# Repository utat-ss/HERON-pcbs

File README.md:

# Printed Circuit Boards (PCBs)

This repository houses Altium PCB designs for the Heron MK II CubeSat project. It contains [pcbs-common](https://github.com/HeronMkII/pcbs-common) as a Git submodule with commonly used schematics.

**Export all schematics and board layouts to PDF files so others can easily view them without using Altium.**

## How to add pcbs-common files into your current Altium project

- Update your GitHub with the pcbs-common submodule

- Run these git commands from your `./pcbs` folder:

```
git submodule init .
git submodule update --remote pcbs-common
```

- Get the files in your current project
- Project → Add Existing to Project → navigate to your copy of pcbs-common → select relevant files for your design.
- Substitute your current subsheets with the pcbs-common versions
- Open properties of target subsheet (the green box) → find the label indicating from where it’s taking the current subsheet → select the ... → navigate to the pcbs-common version in your project → select and OK
- Synchronize the labels to the subsheet with pcbs-common version
- Right click on the green box → sheet actions → synchronize sheet labels → select the pairs of corresponding sheet symbols → select the bottom arrow option (symbol of a beige box to a blue box [this pushes the version from pcbs-common onto the upper level]).
- When you run out of things to link, select the remaining items in the middle column → add (bottom option) → add no ERCs (X symbols) to pins you are not currently using.

## Updating pcbs-common

From the `pcbs` folder:

`$ git submodule update --remote`

This will fetch the latest commit of `pcbs-common` and update your files.

If you get an error about having modified files inside the `pcbs-common` folder, run the following:

```
$ cd pcbs-common
$ git reset --hard
```

This will discard all local changes you have made in the `pcbs-common` folder. Then, run `$ git submodule update --remote` again to download the most updated version of the `pcbs-common` files.

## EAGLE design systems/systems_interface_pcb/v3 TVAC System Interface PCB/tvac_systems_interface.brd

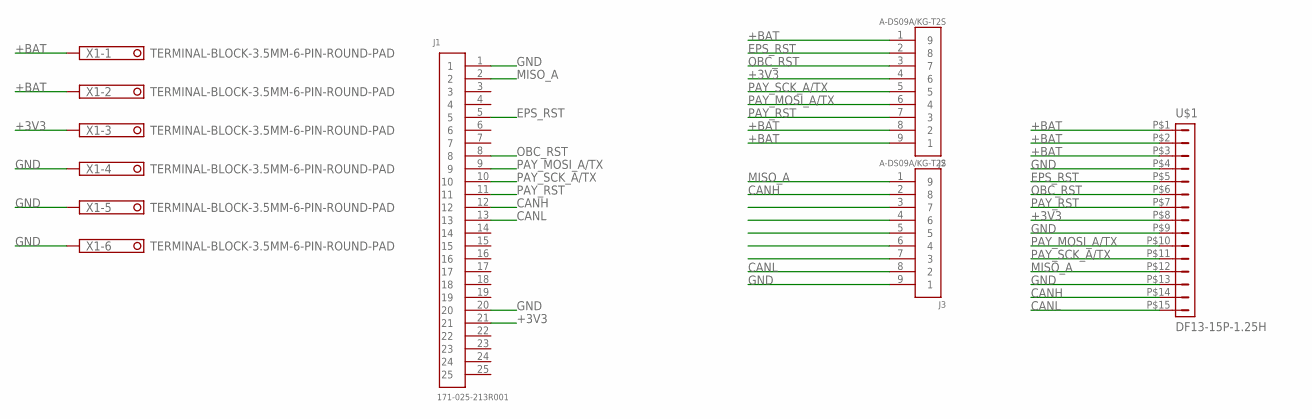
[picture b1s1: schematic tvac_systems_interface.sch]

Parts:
J1: 171-025-213R001
J2, J3: A-DS09A/KG-T2S
U$1: DF13-15P-1.25H; DF13A-15P-1.25H
X1: TERMINAL-BLOCK-3.5MM-6-PIN-ROUND-PAD; TERMINAL-BLOCK-6-PIN-3.5MM-ROUND-PAD

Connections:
+3V3: J1.21, J2.4 (6), U$1.P$8 (8), X1.3
+BAT: J2.1 (9), J2.8 (2), J2.9 (1), U$1.P$1 (1), U$1.P$2 (2), U$1.P$3 (3), X1.1, X1.2
CANH: J1.12, J3.2 (8), U$1.P$14 (14)
CANL: J1.13, J3.8 (2), U$1.P$15 (15)
EPS_RST: J1.5, J2.2 (8), U$1.P$5 (5)
GND: J1.1, J1.20, J3.9 (1), U$1.P$4 (4), U$1.P$9 (9), U$1.P$13 (13), X1.4, X1.5, X1.6
MISO_A: J1.2, J3.1 (9), U$1.P$12 (12)
OBC_RST: J1.8, J2.3 (7), U$1.P$6 (6)
PAY_MOSI_A/TX: J1.9, J2.6 (4), U$1.P$10 (10)
PAY_RST: J1.11, J2.7 (3), U$1.P$7 (7)
PAY_SCK_A/TX: J1.10, J2.5, U$1.P$11 (11)

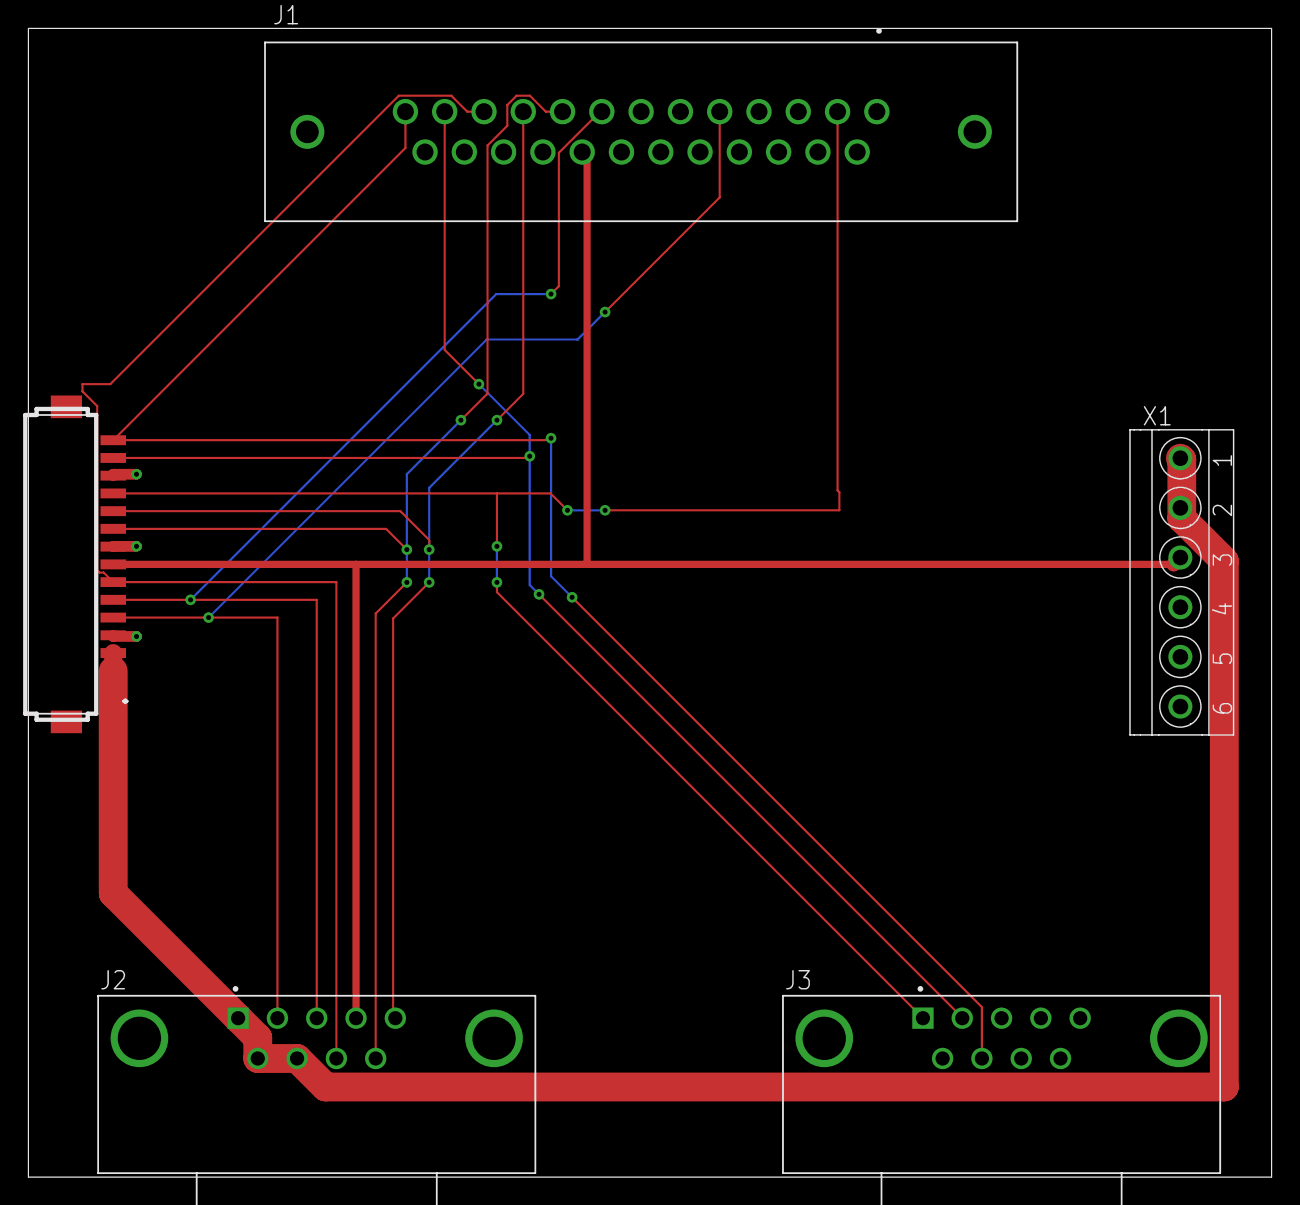
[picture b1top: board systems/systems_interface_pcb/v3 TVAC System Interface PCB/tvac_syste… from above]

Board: 2 copper layers, 87.6 x 81.0 mm, 5 parts (0 on the bottom side), 11 nets.

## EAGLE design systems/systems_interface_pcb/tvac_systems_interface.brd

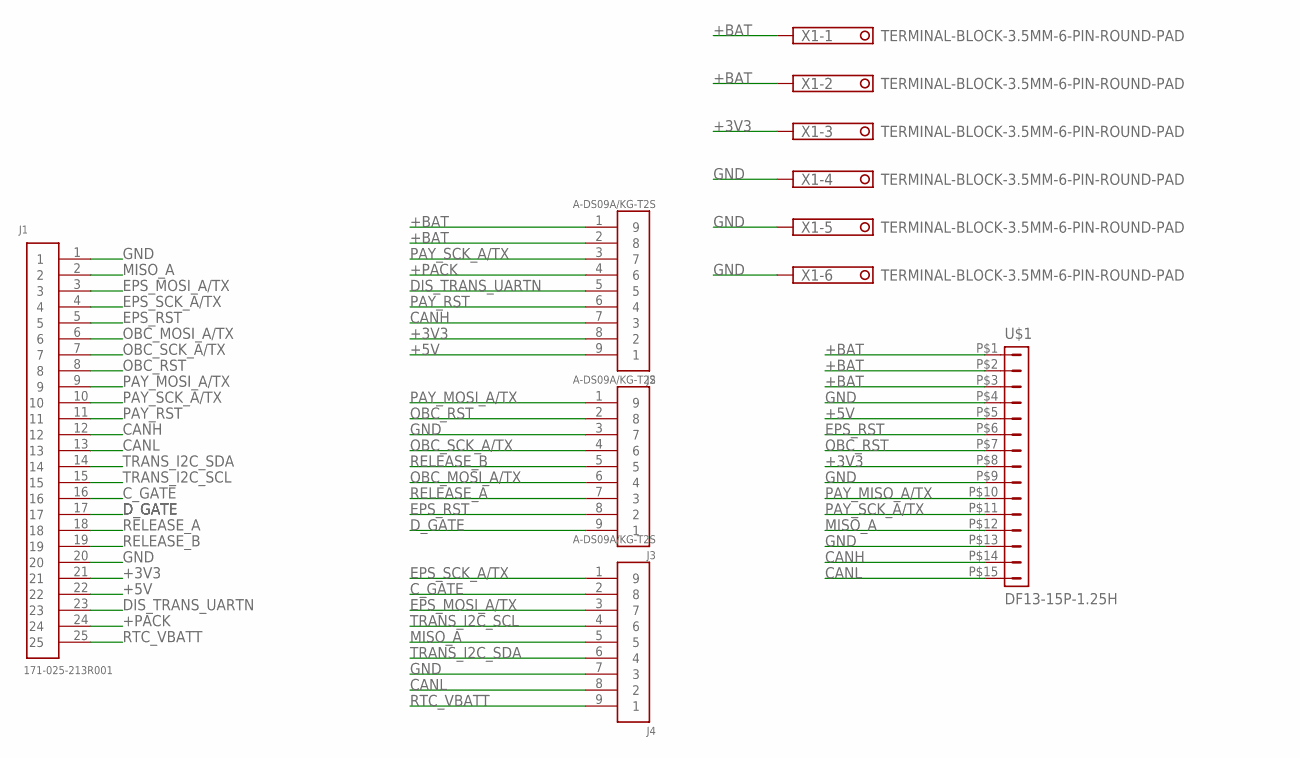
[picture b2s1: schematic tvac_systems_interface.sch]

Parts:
J1: 171-025-213R001
J2, J3, J4: A-DS09A/KG-T2S
U$1: DF13-15P-1.25H; DF13A-15P-1.25H
X1: TERMINAL-BLOCK-3.5MM-6-PIN-ROUND-PAD; TERMINAL-BLOCK-6-PIN-3.5MM-ROUND-PAD

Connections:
+3V3: J1.21, J2.8 (2), U$1.P$8 (8), X1.3
+5V: J1.22, J2.9 (1), U$1.P$5 (5)
+BAT: J2.1 (9), J2.2 (8), U$1.P$1 (1), U$1.P$2 (2), U$1.P$3 (3), X1.1, X1.2
+PACK: J1.24, J2.4 (6)
CANH: J1.12, J2.7 (3), U$1.P$14 (14)
CANL: J1.13, J4.8 (2), U$1.P$15 (15)
C_GATE: J1.16, J4.2 (8)
DIS_TRANS_UARTN: J1.23, J2.5
D_GATE: J1.17, J3.9 (1)
EPS_MOSI_A/TX: J1.3, J4.3 (7)
EPS_RST: J1.5, J3.8 (2), U$1.P$6 (6)
EPS_SCK_A/TX: J1.4, J4.1 (9)
GND: J1.1, J1.20, J3.3 (7), J4.7 (3), U$1.P$4 (4), U$1.P$9 (9), U$1.P$13 (13), X1.4, X1.5, X1.6
MISO_A: J1.2, J4.5, U$1.P$12 (12)
OBC_MOSI_A/TX: J1.6, J3.6 (4)
OBC_RST: J1.8, J3.2 (8), U$1.P$7 (7)
OBC_SCK_A/TX: J1.7, J3.4 (6)
PAY_MISO_A/TX: U$1.P$10 (10)
PAY_MOSI_A/TX: J1.9, J3.1 (9)
PAY_RST: J1.11, J2.6 (4)
PAY_SCK_A/TX: J1.10, J2.3 (7), U$1.P$11 (11)
RELEASE_A: J1.18, J3.7 (3)
RELEASE_B: J1.19, J3.5
RTC_VBATT: J1.25, J4.9 (1)
TRANS_I2C_SCL: J1.15, J4.4 (6)
TRANS_I2C_SDA: J1.14, J4.6 (4)

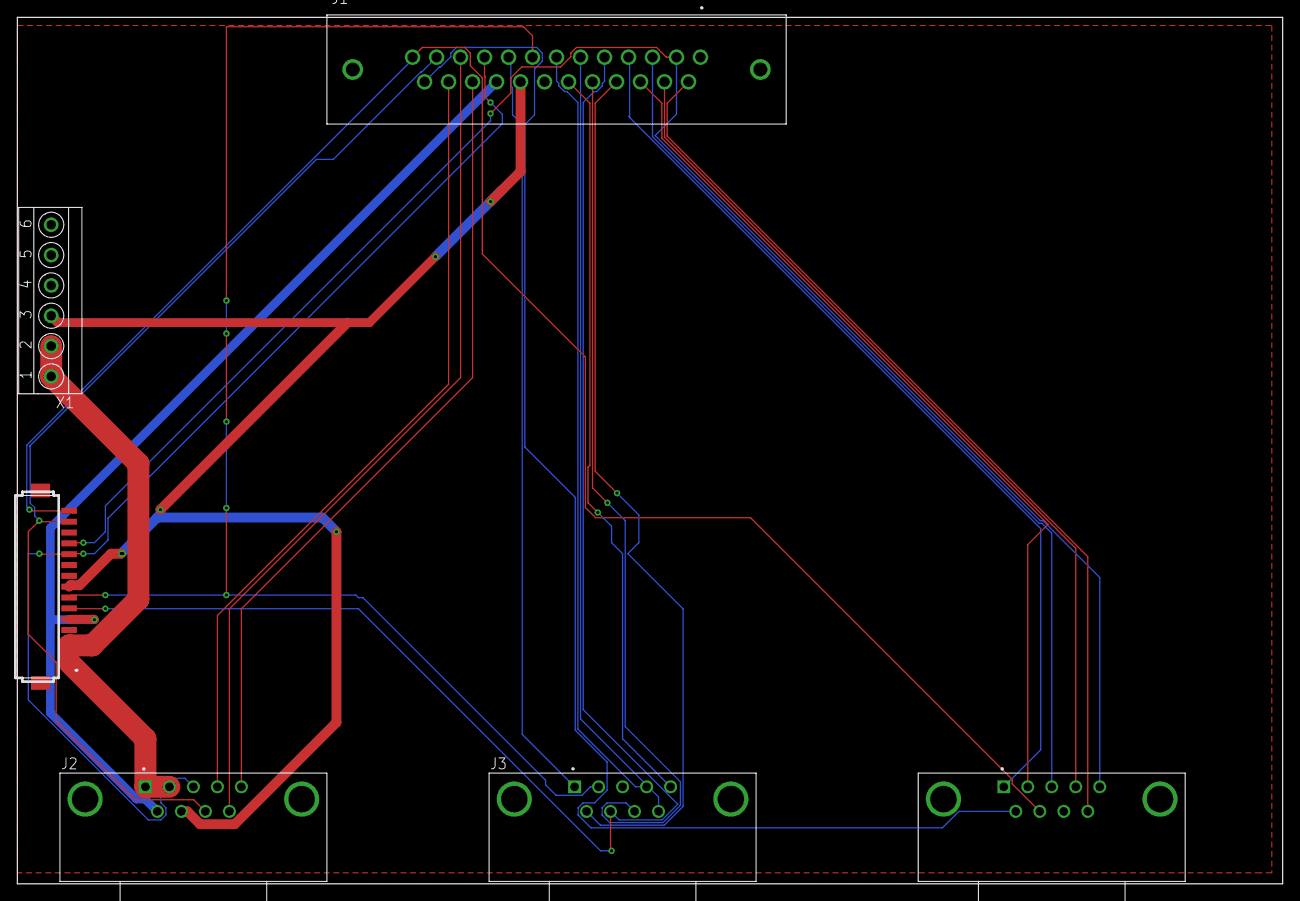
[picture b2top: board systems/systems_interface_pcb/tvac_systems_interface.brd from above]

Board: 2 copper layers, 146.0 x 100.0 mm, 6 parts (0 on the bottom side), 25 nets.

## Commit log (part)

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2019-08-04 [PAY-SSM] imported schematic changes to pay-ssm-v4-2
2019-08-04 Fixed inductor IND-IHLP-1212BZ-11 footprint & add in 3D model
2019-08-04 [EPS] minor changes to pours and heater layout
2019-08-04 [SYS] Swap batt screw terminal pins
2019-08-05 [EPS] added header for converter testing, layout prep for routing
2019-08-06 [PAY-SSM] BOOST-10V re-placement
2019-08-06 [PAY-SSM] BOOST-6V placement finished
2019-08-07 [SYS] Replace batt connector, label 3V3 releases, remove RTC LED
2019-08-07 [SYS] Add VCC/GND, BATT, and SOLAR pours
2019-08-07 [PAY-SSM] finished ALL component placement
2019-08-07 Routed majority of heater control
2019-08-07 [EPS] routed solar panel buffer signals to buffers
2019-08-07 [PAY-SSM] Fixed annoying textboxes in schematics
2019-08-07 Added 3D bodies to things w/o 3D bodies
2019-08-07 [SYS] Continued routing programming and debugging
2019-08-08 [OBC] Routed most of MCU and CAN transceiver
2019-08-08 [SYS] Route DSUB to debugging headers
2019-08-08 [EPS] Routed most of digital
2019-08-08 [EPS] Minor change
2019-08-08 [SYS] More routing
2019-08-09 [SYS] More programming routing
2019-08-09 [SYS] Change programming room scope
2019-08-09 [SYS] Finish whole board routing, add top layer polygons for BATT/SOLAR
2019-08-09 [PAY-SSM] Added debugging header
2019-08-09 [EPS] continued digital routing, gate drive buffer done
2019-08-09 [EPS] small-time routing changes
2019-08-10 [EPS] added ADC bus from modified channel pins
2019-08-10 [OBC] Finished routing, no DRC unrouted net errors
2019-08-10 [EPS] majority of PEX routed, other digital routing coming together
2019-08-10 [PAY-SSM] motor drivers layout done
2019-08-10 Added solar cell footprints and symbols
2019-08-10 [EPS] tweaks from today's review
2019-08-11 [SYS] Use pcbs-common low-profile headers, rearrange programming layout
2019-08-11 [EPS] More minor routing
2019-08-11 [EPS] Routing almost done, still need to remove gate drive buffer
2019-08-11 [PAY-SSM] fixed boost connections, relayout high-power
2019-08-11 [EPS] EPS technically done routing, removed GDB from solar schematic
2019-08-11 Finished solar panels
2019-08-12 [PAY-SSM] finished high-power layout
2019-08-13 [SYS] Create via stitching for BATT and SOLAR
2019-08-13 [EPS] added level shifter to library and routed
2019-08-13 [EPS] Added diodes to EPS PCB
2019-08-13 Whoops forgot to save the LibPkg
2019-08-14 [SYS] Routing cleanup
2019-08-14 [SYS] More routing cleanup
2019-08-14 [PAY-SSM] motor drivers re-layout
2019-08-14 [PAY-SSM] Changed mounting vias to pads
2019-08-14 [PAY-SSM] thermistor ADCs done
2019-08-15 [SYS] Add Route Tool Path, modify outjob for fabrication outputs
2019-08-15 [PAY-SSM] Generated Gerber files
2019-08-15 Exported gerber files, fixed bypassing, silk screen resizing, tinting vias
2019-08-15 [EPS] project outputs
2019-08-15 [Solar] Added solar mounting pads
2019-08-15 [OBC] Updated fabrication outputs
2019-08-15 [PAY-SSM] corrected the silkscreen for gerber files
2019-08-15 [PAY-SSM] Finished pex layout
2019-08-16 Rename syspcb and sys_debug_pcb to systems_pcb
2019-08-16 [SYS] Fix project file associations with consistent naming, delete outdated files
2019-08-16 [PAY-SSM] done all pexs and adcs
2019-08-17 [SYS] Redo BATT pours on all layers, adjust SOLAR pours and conn placement
2019-08-17 [EPS] improvements from electronics systems meeting
2019-08-17 [SYS] Fix Route Tool Path on all plots in OutJob
2019-08-17 [EPS] improved routing on DSUB and micro
2019-08-17 [EPS] Added filter circuit with spec'd values
2019-08-17 [OBC] Silkscreen and misc fixes
2019-08-18 [SYS] Add BATT and SOLAR overlay dividers, lots of routing cleanup
2019-08-18 [SYS] Add HERON logo
2019-08-18 [PAY-SSM] pcb revision to 4.3
2019-08-18 [SYS] Wave all necessary silkscreen clearance and off-board violations
2019-08-18 [EPS] Added new OBC step file to board
2019-08-18 [SSM] Finished flipping heaters connectors
2019-08-19 [EPS] Added TVS diode to library
2019-08-19 [EPS] Added footprint and symbol for schottky diode
2019-08-19 [EPS] Added diodes again
2019-08-19 [EPS] some library updates for the programming header
2019-08-19 [SSM] more digital buses
2019-08-19 [EPS] open heart surgery has begun on EPS digital
2019-08-19 [EPS] rotated some connectors, moved battery connector into board
2019-08-19 [SSM] 95% routing done
2019-08-20 [SYS] Minor placement and routing improvements
2019-08-20 [EPS] starting routing of butterfly connector
2019-08-20 [SYS] Create title blocks and parameters for schematic sheets
2019-08-20 [EPS] butterfly routing done
2019-08-20 [EPS] rerouted rotated connector, moved PAY load switch setup left
2019-08-20 [SSM] Top silk done
2019-08-21 [OBC] Added Bruno's review changes
2019-08-21 [SSM] done silkscreen
2019-08-22 [Solar] moved solar panel diodes to de-conflict EPS battery connector
2019-08-22 [EPS] added hermetic cutout and begun rererouting
    SHOT THROUGH THE HEART
    And the hermetic's to blame.
    It gives PCB design a bad name.
    .....
2019-08-22 [SSM] minor changes
2019-08-23 [SYS] Implement pullup/pulldown resistors for programming LED buffers
2019-08-23 [SSM] done power re-route
2019-08-24 [SYS] Swap CANH and CANL on buffer, finish CAN LED routing changes
2019-08-24 [SYS] Waive remaining DRC violations
2019-08-24 [SYS] Schematic and routing cleanup
2019-08-24 [EPS] minor bus rerouting, moving RTC batt around [SYS] updated footprint for 2x2 header
2019-08-24 [EPS] bus rerouted for cutout
2019-08-24 [EPS] minor rerouting to programming headers, etc
2019-08-25 [EPS] Added battery input filters
2019-08-25 [EPS] Added missing schematic documents from pcb-common
    I was missing links to pcb-common schematics - Recently just added them back in
2019-08-25 [EPS] re-annotated components
2019-08-25 [EPS] Properly re-annotated schematic with updated PCBs common
2019-08-25 [EPS] Made changes to solar shunt footprint
2019-08-25 [EPS] psuhed in connectors into board by 0.5mm
2019-08-25 [EPS] Added silkscreen boxes around components
2019-08-25 [EPS] Curved cutout corners
2019-08-25 [EPS] Added minor labeling
2019-08-25 [EPS] added misc labels and battery filter
2019-08-25 [EPS] added to silkscreen
2019-08-25 [EPS] Fixed some text, added test points
    Test points added to:
    - Boost
    - Batt pro
2019-08-26 [pay-led] Added pay-led-2 variant
2019-08-26 [SSM] break out boost EN pin, add BATT volt mon, some other minor fixes
2019-08-26 [EPS] Fixed some errors on DRC
2019-08-26 [EPS] fixed more DRC errors
2019-08-26 [SSM] updated ssm-optical connector
2019-08-26 [EPS] addes preliminary DF13/Load switch RBF replacement
2019-08-27 [EPS] Fixed more DRC violations
2019-08-27 [EPS] More DRC
2019-08-27 [EPS] Fixed boost layout, laid out DF-13
2019-08-27 [SSM] fixed most motors bus
2019-08-28 [EPS] Routed DF13 and load switch
2019-08-28 [SSM] more digital routing
2019-08-28 [EPS] Routing, DRCs
2019-08-28 [EPS] Exported CAD for thermal
2019-08-28 Re-routed DF13, fixed some DRCs, 5 remaining, specd filter parts
2019-08-29 [SYS] Small polygon fixes
2019-08-29 [SYS] Fix schematic title blocks, embed CAN logic voltage image
2019-08-29 [EPS] Added pin 1 to SN74LV1 symbols, made TC7WB67 symbol and replaced it, configured it to active high, replaced pull up with pull down, finally found that shelved polygon DRC error
2019-08-30 Add files via upload
    splits db25 on sys_pcb into 3x db9's to pass through the thermal chamber
2019-08-30 [EPS] Fixed DRC Errors
2019-08-30 [EPS] minor fix to RBF schematic
2019-08-30 [EPS] Fixed battery do not invert terminal sign
2019-08-30 [EPS] Fixed routing
2019-08-30 [EPS] Added silkscreen for the shits and giggles.
2019-08-30 [EPS] non-silkscreen DRCs are fixed
2019-08-30 [SSM] fixed all DRC errors besides Silk To Solder Mask Clearance
2019-08-30 [EPS] more review changes
2019-08-30 [OBC/LIB] added 3D models to OBC
2019-08-30 [EPS] added OBC CAD model to EPS
2019-08-30 [SSM] confirmed ssm-optical pin out, added utat logo
2019-08-31 [OBC] Delete old schematics and files now in pcbs-common or repo root
2019-08-31 [OBC] Rename obc-comm to obc, remove unused files
2019-08-31 [OBC] Reannotate and recompile project
2019-08-31 [Heron General Deleted heron-general folder which keeps appearing, fixed multi-layer plating on SLW 15-pin header
2019-08-31 [OBC] Update 15-pin debug header footprint with plating
2019-08-31 [OBC] Change track width from 0.254mm -> 0.2mm
2019-08-31 [OBC] Disable all rooms except flash
2019-08-31 [OBC] Misc DRC and silkscreen fixes, cleanup
2019-09-01 pay limit switch pcb
2019-09-01 [OBC] More DRC fixes
2019-09-01 [EPS] tweaked silkscreen designators
2019-09-01 [OBC] Change 0603 resistors/capacitors to 0402s
2019-09-01 [OBC] Layout cleanup
2019-09-01 [OBC] Waive DRC violations
2019-09-01 [OBC] Update BOM and outjob
2019-09-01 [OBC] Move some components to bottom layer, misc layout cleanup
2019-09-01 [OBC] Add HERON logo, move UTAT logo
2019-09-01 [EPS] added 10uF bypassing to DAC and INA214
2019-09-02 [EPS] new gerber exports and zip file, small routing changes
2019-09-02 [OBC] cut corner to allow wiring room on EPS and created new outputs
2019-09-02 [OBC] Misc layout changes, re-exported gerbers
2019-09-02 [OBC] Small layout fixes
2019-09-02 [SYS] Small schematic properties cleanup
2019-09-03 [SYS] Update project
2019-09-03 [SYS] Change comparator output pullups from 1k -> 10k
2019-09-03 [OBC] Improve CAN transceiver layout from datasheet guide, misc layout fixes
2019-09-03 [EPS] routing fixes from review and new exports
2019-09-04 [SYS] Small placement fixes for BATT/SOLAR
2019-09-04 [SYS] Adjust OutJob settings to match OneNote specification
2019-09-04 [EPS] EPS BOM filled out and new exports made
2019-09-04 [SSM] re-layout ADC, re-gen gerbers
2019-09-04 [EPS] updated some components in BOM
2019-09-04 [EPS] fit check w/ OBC STEP
2019-09-06 [SSM] Finished fixing some logic power paths
2019-09-06 [SSM] re-exported Gerbers and zip file
2019-09-09 [SSM] more tweaking, fixed heater LEDs
2019-09-10 [SSM] Done schematics numbering, exported schematic PDF prints
2019-09-10 [SSM] Saved project
2019-09-11 [SSM] Updated board size, fixed DRC, updated gerbers
2019-09-11 re-exported schematics PDF for PAY-SSM and EPS
2019-09-12 re-exported gerbers for stensil order (EPS, OBC, SYS, SSM)
2019-09-13 [SSM] re-generated gerbers and added new zip file
2019-09-16 [pay-led] exported new gerbers
2019-09-17 using Eagle, with DF13 connector and terminal blocks
2019-09-18 [OBC] BOM completed
2019-09-18 New BOMs for flight boards
2019-09-18 Compiled flight BOM excel sheet
2019-09-19 updated SSM flight BOM in compiled flight BOM excel, [SSM] minor BOM update
2019-09-20 Edits to BOM
2019-09-20 [SSM] final BOM update
2019-09-26 [PAY] limit switch redesign and project outputs
2019-09-30 [SSM] minor schematic changes, re-numbering
2019-09-30 [SSM] re-naming schematics for consistency
2019-10-02 [EPS] BOM fixes and re-export
2019-10-23 rescoped TVAC, only powering heaters
2019-10-25 Add files via upload
    GND shielding of data lines
2019-10-28 flipped D25 so cable is plugged into side of board
2019-10-28 [SSM] fixed ADC 2V5REF
2019-10-29 Added new zip file of TVAC board v4 gerbers
2019-10-29 [SSM] partial connector silkscreen fixes
2019-10-29 [SSM] GPIO done, re-layout SPI lines
2019-10-29 [SSM] converted UTAT logo to bitmap from true font
2019-10-30 [SSM] finished connecting all traces
2019-10-30 [SSM] Finished silkscreen
2019-10-31 [SSM] revision to pay-ssm v4-5
2019-11-04 [SSM] exported gerbers and schematic prints
2019-11-06 [SSM] more regulator layouts improvements, re-gen new gerbers
2019-11-06 [SSM] final gerbers
2019-11-27 [SSM] BOM update for v4.5
2020-01-10 [EPS] Battpro inline board
2020-01-14 [SSM] boost converters volt div res value correction
2020-05-15 project template v1.0 done
